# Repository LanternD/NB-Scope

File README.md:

# NB-Scope

Hardware and software design for NB-Scope.

NB-Scope is employed in our MobiCom 20 paper "Understanding Power Consumption of NB-IoT in the Wild: Tool and Large-scale Measuremen" [DOI](https://doi.org/10.1145/3372224.3419212).

Please check the README.md under the folders for more details.

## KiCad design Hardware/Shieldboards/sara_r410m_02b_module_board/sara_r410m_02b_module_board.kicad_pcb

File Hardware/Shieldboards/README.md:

# Important Note

- The majority of the modules here can be soldered by hand, except Quectel BG96 and uBlox SARA-R410M-02B.
  - If you solder the SARA-R410M-02B **by yourself** (customizing the stencil and applying the solder paste), instead of using the SMT service, you need to shrink the size of all the pads of the SARA-R410M-02B footprint! Otherwise they are likely to get short-circuited.
  - Before

  - After

- All the shieldboards have a RESET button for the module.
- There is a design compatibility issue in those modules with a "PWR_KEY" pin, including SARA-R410M-02B, BG96, BC26, and BC66. The pin requires an open collector transistor to enable, which I use different hardware designs to take care of it across different version of the board. Here is the summary:
  - Node mainboard v3.2 + BC26/BC66/SARA shieldboard: no modification needed.
  - Node mainboard v3.2 + SARA shieldboard: use GPIO_L4 as the `PWRKEY` control pin. The software code can handle this.
  - Node mainboard v3.1 + BC26/BC66/BG96 shieldboard: need to fixed by the `pwr_key_addon` in "Auxilliary Boards" folder (**Not recommended**).
  - Node mainboard v3.1 + SARA shieldboard: use GPIO_L4 as the `PWRKEY` control pin (**Not recommended**).

# Photos

Note: the pin headers in the photos face up, but in reality they should be soldered on the other side of the board, facing down, such that the shieldboard can be docked to the mainboard.

## Quectel BC26 (BC66) Shieldboard

Note: BC66 is almost identical to BC26 board, except for the swap between UART Tx and Rx pin.

## Quectel BC28 Shieldboard

## Quectel BC95/BC35 Shieldboard

## Gosuncn ME3616 Shieldboard

## Quectel BG96/BG36 Shieldboard

## uBlox SARA-R410M-02B Shieldboard

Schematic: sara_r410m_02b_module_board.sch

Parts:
C1, C2, C3, C4, C5, C6, C7, C8: 100nF; C_0603_1608Metric
D1: LED; LED_0805_2012Metric
J1: 1865; SMA_Antenna
J2: Left_Conn; PinHeader_1x22_P1.27mm_Vertical
J3: Right_Conn; PinHeader_1x22_P1.27mm_Vertical
J4: USB_DET_Conn; PinHeader_1x02_P1.27mm_Vertical
Q1, Q2: MMBT3904; SOT-23
R1: 0; R_0603_1608Metric
R2: 4.7k; R_0603_1608Metric
R3: 47k; R_0603_1608Metric
R5, R22: 2.2k; R_0603_1608Metric
SW1: SW_Push; SMD_Switch
T1: M_PWR_KEY; test_pad
U1: uBlox_SARA-R410M-02B; Ublox_SARA-R410M-02B
U2, U3: TXB0304RUT; Texas_R_PUQFN-N12

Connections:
/B_SPI_CLK-I2S_CLK: J2.7
/B_SPI_CS-I2S_CS: J2.8
/B_SPI_MISO-I2S_RXD: J2.5
/B_SPI_MOSI-I2S_WA: J2.6
/GPIO_L1: J2.3, U2.7
/GPIO_L2: J2.9, U2.8
/GPIO_L3: J2.21, U2.9
/GPIO_L4: J2.22, R2.2
/GPIO_R1: J3.8, U3.10
/GPIO_R2: J3.17
/GPIO_R3: J3.18
/M_ADC: J2.13
/M_AP_READY: J2.20
/M_AUX_UART_Rx: J3.14
/M_AUX_UART_Tx: J3.13
/M_DBG_UART_Rx: J3.12
/M_DBG_UART_TX: J3.11
/M_MAIN_UART_Rx: J2.15, U1.12 (TXD)
/M_MAIN_UART_Tx: J2.14, U1.13 (RXD)
/M_NET_LED: J3.15, U1.16 (GPIO1)
/M_PWRKEY: J2.16
/M_PWR_KEY_NEW: Q2.3, T1.1, U1.15 (PWR_ON)
/M_RESET: J2.17, U2.10
/M_RI: J3.16, U1.7 (RI)
/M_SCL: J3.10, U3.8
/M_SDA: J3.9, U3.9
/M_USB_DM: J2.12, U1.28 (USB_D-)
/M_USB_DP: J2.11, U1.29 (USB_D+)
/M_USB_VBUS: J2.10, J4.1
/M_VDD_OUT: C4.2, C7.2, J2.19, U1.4 (V_INT), U2.1, U2.12, U3.1, U3.12
/PSM_EINT: J2.18
/PSM_IND: J2.4
/SARA_GPIO2: U1.23 (GPIO2), U2.4
/SARA_GPIO3: U1.24 (GPIO3), U2.3
/SARA_GPIO5: U1.42 (GPIO5), U3.2
/SARA_GPIO6: U1.19 (GPIO6), U2.5
/SARA_RESET: C1.1, SW1.2, U1.18 (RESET_N), U2.2
/SARA_SCL: U1.27 (SCL), U3.4
/SARA_SDA: U1.26 (SDA), U3.3
/SARA_STATUS_LED: R22.2, U1.25 (GPIO4)
/SIM_CLK: J3.6, U1.38 (SIM_CLK)
/SIM_IO: J3.5, U1.39 (SIM_IO)
/SIM_RST: J3.4, U1.40 (SIM_RST)
/V_SIM: J3.3, U1.41 (VSIM)
GND: C1.2, C2.2, C3.2, C4.1, C5.1, C6.2, C7.1, C8.1, J1.GND1, J1.GND2, J1.GND3, J1.GND4, J3.7, J3.19, J3.20, J3.21, J3.22, Q1.2, Q2.2, R3.1, SW1.1, U1.1 (GND), U1.3 (GND), U1.5 (GND), U1.14 (GND), U1.20 (GND), U1.21 (GND), U1.22 (GND), U1.30 (GND), U1.32 (GND), U1.43 (GND), U1.50 (GND), U1.54 (GND), U1.55 (GND), U1.57 (GND), U1.58 (GND), U1.59 (GND), U1.60 (GND), U1.61 (GND), U1.63 (GND), U1.64 (GND), U1.65 (GND), U1.66 (GND), U1.67 (GND), U1.68 (GND), U1.69 (GND), U1.70 (GND), U1.71 (GND), U1.72 (GND), U1.73 (GND), U1.74 (GND), U1.75 (GND), U1.76 (GND), U1.77 (GND), U1.78 (GND), U1.79 (GND), U1.80 (GND), U1.81 (GND), U1.82 (GND), U1.83 (GND), U1.84 (GND), U1.85 (GND), U1.86 (GND), U1.87 (GND), U1.88 (GND), U1.89 (GND), U1.90 (GND), U1.91 (GND), U1.92 (GND), U1.93 (GND), U1.94 (GND), U1.95 (GND), U1.96 (GND), U2.6, U3.6
unnamed: C2.1, R1.2, U1.56 (ANT)
unnamed: C3.1, J1.P, R1.1
unnamed: D1.1 (K), Q1.3
unnamed: D1.2 (A), R5.2
unnamed: J4.2, U1.17 (VUSB_DET)
unnamed: Q1.1, R22.1
unnamed: Q2.1, R2.1, R3.2

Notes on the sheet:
Connectors to the module board
From Node Base
Reset Buttom Circuit
For right hand part
For left hand part
Note: no pull-up resistor needed (has internal one)
Note: The SARA uses the STUPID ITU-T V.24 recommendation. So the "RXD" on the module means the RXD of the MCU. It actually outputs data.

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
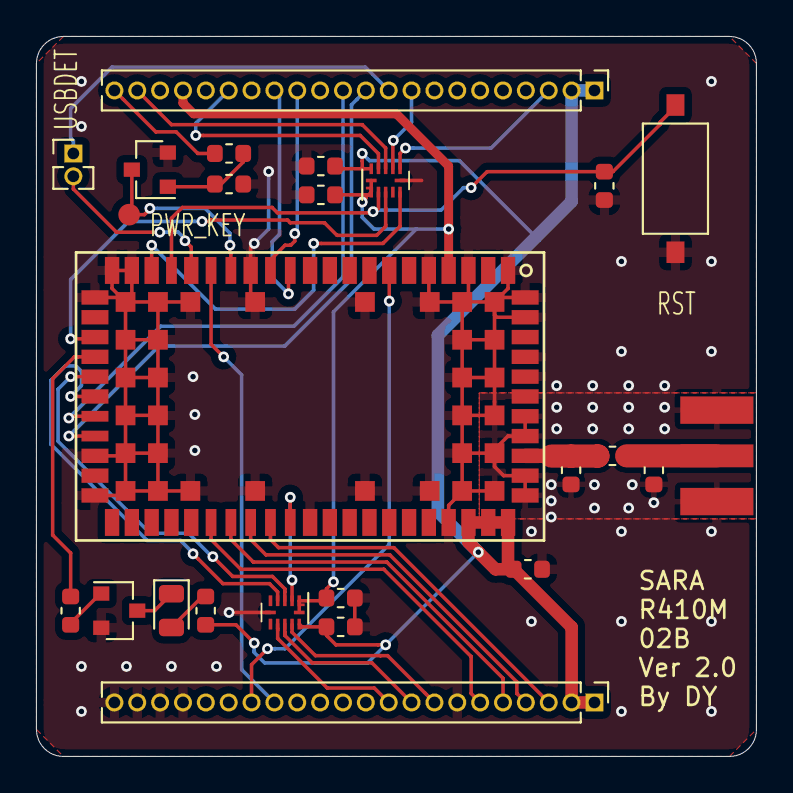
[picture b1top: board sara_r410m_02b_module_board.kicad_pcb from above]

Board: 2 copper layers, 40.0 x 40.0 mm, 25 parts (0 on the bottom side), 38 nets.

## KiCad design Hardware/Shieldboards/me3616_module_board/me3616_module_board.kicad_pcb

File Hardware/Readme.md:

# Hardware Guideline

## Overview

This folder contains the NB-Scope nodes hardware designs. Specifically, we have a folder for the mainboard, a folder for all the shieldboard for NB-Scope, and a folder for the auxilliary boards.

### Mainboard

The mainboard has 3 versions. **Please use ver 3.2**. The outdated versions are for reference only. They may work but not very stable. Ver 1.0 and 2.0 are not for NB-Scope projects, thus are omitted.

### Shieldboards

We have 7 types of shieldboard designs, supporting up to 9 types of different NB-IoT modules, including:

- Quectel BC28
- Quectel BC35
- Quectel BC26
- Quectel BC66
- Quectel BC95 (Not tested)
- Quectel BG36 (Not tested)
- Quectel BG96
- Gosuncn ME3616
- uBlox SARA-R410M-02B

(Quectel BG36/BG96 and Quectel BC35/BC95, have the same pin assignment, respectively.)

The module PCB project names should be straight-forward in the "Shieldboards" folder.

### Auxilliary boards

- Current sensing calibration board
- Firmware upgrade extension board
- Moulde benchmark extension board
- PWR_KEY addon

### Libraries

If you encounter missing symbol/footprint problem when opening the schematic or PCB files, please import them in the `Libraries` folder. The missing libraries should be a subset of the available footprints.

### Materials

I put the related documents related to hardware design here, including NB-IoT module summary and various datasheets.

## EDA environment

The software to open the projects is [KiCad](https://kicad-pcb.org/) (Pronounced as "key-cad").

PLEASE use the **Nightly-build** version of KiCad because the projects are created by that. The projects are not backward compatible.

To open the 3D viewer, click "View->3D Viewer" (<kbd>⌥+3</kbd> on Mac or <kbd>Alt+3</kbd> on other operating systems) in the `Pcbnew` software menu.

If you use the latest version of KiCad to open `.sch` files, `Eeschema`, the software component to edit schematic, will ask you to convert the `.sch` into `.kicad_sch`. Just go ahead and follow the instruction in KiCad.

You can generate all the files for fabrication in `Pcbnew` software module in KiCad.

## Project structure

- `<project_name>.pro`: project main file.
- `<project_name>.sch` or `<project_name>.kicad_sch`: project schematic design. If `.sch` and `.kicad_sch` co-exist, use the `.kicad_sch` one.
- `<project_name>.kicad_pcb`: project PCB design.
- `Exported Files` folder: exported/generated files from the projects, including Gerber files, bill of materials (BOM), positioning files (for SMT process), and other board 3D views or documents. I suggest you double check the project schematic and pcb designs, then generate these fabrication files again by yourself, instead of sending the Gerber files to manufacturers directly.

There are some KiCad generated backup or middle files. I forget to remove them before committing. You may ignore or edit them. They have the following patterns:

- `fp-info-cache`
- `<project name>-cache.lib`
- `<project name>-rescue.dcm`
- `<project name>-rescue.lib`
- `<project name>.kicad_pcb-bak`
- `<project name>.sch-bak`
- `sys-lib-table`

## Click into their corresponding folders for more details

If you have any questions, please send me an email to "yangdeli at msu.edu".

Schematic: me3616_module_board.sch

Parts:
C1, C2, C3, C7: 100nF; C_0603_1608Metric
J1: 1865; SMA_Antenna
J2: USB_V_BUS_EN; PinHeader_1x02_P1.27mm_Vertical
J12: Left_Conn; PinHeader_1x22_P1.27mm_Vertical
J13: Right_Conn; PinHeader_1x22_P1.27mm_Vertical
Q1, Q2: MMBT3904; SOT-23
R1: 0; R_0603_1608Metric
R2, R4: 4.7k; R_0603_1608Metric
R3, R5: 47k; R_0603_1608Metric
SW2: SW_Push; SMD_Switch
T2: ME3616_MAIN_RXD; test_pad
T3: ME3616_DBG_RXD; test_pad
T4: ME3616_MAIN_TXD; test_pad
T5: ME3616_DBG_TXD; test_pad
U1: ME3616; ZTE_ME3616

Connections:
+3V3: C1.1, J2.2, J12.1, J12.2, J13.1, J13.2, U1.31 (VCC_BB), U1.32 (VCC_RF)
/B_SPI_CLK-I2S_CLK: J12.7
/B_SPI_CS-I2S_CS: J12.8
/B_SPI_MISO-I2S_RXD: J12.5
/B_SPI_MOSI-I2S_WA: J12.6
/GPIO_L1: J12.3, U1.34 (GPIO1)
/GPIO_L2: J12.9, U1.35 (GPIO2)
/GPIO_L3: J12.21
/GPIO_L4: J12.22, R2.2
/GPIO_R1: J13.8
/GPIO_R2: J13.17
/GPIO_R3: J13.18
/ME3616_POWER_ON: Q2.3, U1.19 (POWER_ON)
/ME3616_RESET: Q1.3, U1.17 (RESET)
/M_ADC: J12.13
/M_AP_READY: J12.20
/M_AUX_UART_RX: J13.14
/M_AUX_UART_TX: J13.13
/M_DBG_UART_RX: J13.12, T3.1, U1.2 (UART_DEBUG_RXD)
/M_DBG_UART_TX: J13.11, T5.1, U1.1 (UART_BEBUG_TXD)
/M_MAIN_UART_RX: J12.15, T2.1, U1.10 (UART1_RXD)
/M_MAIN_UART_TX: J12.14, T4.1, U1.9 (UART1_TXD)
/M_NET_LED: J13.15, U1.21 (SYS_STATE)
/M_PWRKEY: J12.16
/M_RESET: C7.1, J12.17, R4.2, SW2.2
/M_RI: J13.16
/M_SCL: J13.10
/M_SDA: J13.9
/M_USB_DM: J12.12, U1.39 (USB_DM)
/M_USB_DP: J12.11, U1.40 (USB_DP)
/M_USB_VBUS: J12.10
/M_VDD_OUT: J12.19, U1.20 (VCC1V8_OUT)
/PSM_EINT: J12.18, U1.18 (WAKEUP_IN)
/PSM_IND: J12.4
/SIM_CLK: J13.6, U1.13 (USIM_CLK)
/SIM_IO: J13.5, U1.14 (USIM_DATA)
/SIM_RST: J13.4, U1.12 (USIM_RESET)
/V_SIM: J13.3, U1.15 (USIM_VCC)
GND: C1.2, C2.2, C3.2, C7.2, J1.GND1, J1.GND2, J1.GND3, J1.GND4, J13.7, J13.19, J13.20, J13.21, J13.22, Q1.2, Q2.2, R3.1, R5.1, SW2.1, U1.22 (GND), U1.23 (GND), U1.25 (GND), U1.26 (GND), U1.28 (GND), U1.29 (GND), U1.30 (GND)
unnamed: C2.1, R1.2, U1.27 (MAIN_ANT)
unnamed: C3.1, J1.P, R1.1
unnamed: J2.1, U1.33 (VBUS_3V3)
unnamed: Q1.1, R4.1, R5.2
unnamed: Q2.1, R2.1, R3.2

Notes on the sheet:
Note: The ME3616 uses the LED on the base board.
Connectors to the module board
From Node Base
ME3616 Onboard Reset Circuit (No pull-up needed, but add one if this circuit doesn't work)

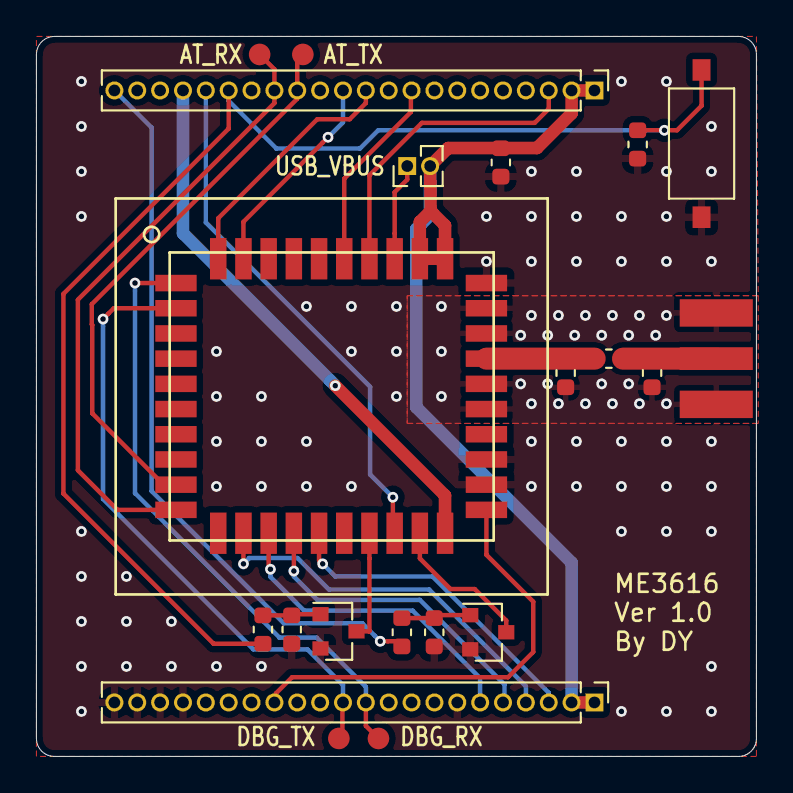
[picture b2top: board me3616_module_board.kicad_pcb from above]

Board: 2 copper layers, 40.0 x 40.0 mm, 21 parts (0 on the bottom side), 26 nets.

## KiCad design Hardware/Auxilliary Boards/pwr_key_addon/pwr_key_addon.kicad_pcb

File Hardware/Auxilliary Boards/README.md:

# Introduction

Auxilliary boards are used to extend the capability of the mainboard and shieldboard, as well as to calibrate the current sensors.

# Current Calibration Board

Since the 0.1 Ohm current sensing resistors are different, the current sensing should be calibrated as per mainboard. 

You need a series of resistors for this board. The actual resistance does not matter. We just compare the sensor reading with the digital multimeter or power monitor reading.

## How to calibrate

Solder the 1.27 mm pitch headers according to the image above. Then follow the instruction to test the output.

Before calibration, make sure the embedded code runs the "current sensing demo" (`void run_demo8_i_bus_sensing()` in `Software/field-test-control/Src/fm_demo.c`). Check the `main.c` as well. 

The mainboard should be connected to the PC via USB, then the PC should open a serial console to read the data from the board.

Steps:

1. See the figure above.
2. See the figure above.
3. Read and record the external current measurement device output (mA).
4. Read and record the INA226 output via the USB UART. The board will output the current register reading once per second.
5. Repeat the above steps for resistors from 13.3 Ohm to 165 Ohm. The 11 Ohm is not recommended. Do not try the 5.6 Ohm.
6. Calculation as follows:
  
  1. Multiply the register value by 0.018311 to get the current reading of INA226. (Note: if the output is already the current value, you don't need to do this conversion, depending on the output of the embedded program.)
  2. Divide the INA226 current by the meter reading current to get a ratio.
  3. Multiply the ratio with 2778 (the preset INA226 calibration register value) to get the new calibration register value. 
  4. Average all the calibration values to get the final calibration value.
  
Here is a table showing the measurement and calculation example for one of our board.

| Expected current (mA) | Meter reading (mA) | INA226 register reading | Calculated INA226 current (mA) | New calibration value |
|-----------------------|--------------------|-------------------------|--------------------------------|-----------------------|
|                    20 |               20.0 |                    1089 |                      19.940679 |              2786.264 |
|                  48.5 |               49.0 |                    2659 |                      48.688949 |              2795.747 |
|                   100 |               99.5 |                    5484 |                     100.417524 |              2752.517 |
|                   150 |              149.0 |                    8235 |                     150.791085 |              2745.003 |
|                   200 |              198.0 |                   10974 |                     200.944914 |              2737.287 |
|                   248 |                244 |                   13487 |                     246.960457 |              2744.699 |

The final calibration value is the average of the last column, resulting in 2760.

The value you get should not be too far from these value above. The final calibration value is around 2700 - 2900. For the same batch of boards, the standard deviation is less than 50. If you use a different batch of current sensing resistor, the value can deviate up to 150. 

**The new current calibration value should be written into the onboard EEPROM before node deployment.**

Note: you need to calibrate EVERY mainboard.

# Module Benchmark Extension Board

An upgraded version of "Firmware Upgrade Extension Board". It docks the shieldboard for the "real-time benchmark mode" of NB-Scope. It can be used to upgrade the NB-IoT module firmware as well. Basically it pinouts all the necessary connectivity of the UE module, such that we can connect them to other peripherals, such as power monitor and UART. 

The two pin headers are compatible with the mainboard.

The "EXT3V3" is used to connect to the power monitor. For example, the RED terminal of the monitor is connected to the EXT3V3, and the BLACK terminal is connected to the 3V3, repectively. "EXTGND" is likewise.

# Firmware Upgrade Extension Board

This is the predecessor of "Module Benchmark Extension Board". Generally you can ignore this one.

# PWRKEY Addon

A tiny board that simply has a BJT on it. It is used to fixed the PWRKEY pin on the UE modules before ver 3.2 mainboard. If you use the latest version of the mainboard, you can ignore this.

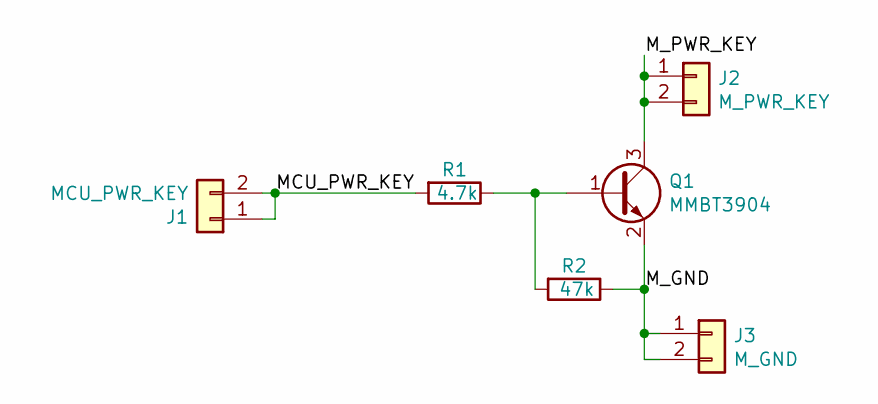
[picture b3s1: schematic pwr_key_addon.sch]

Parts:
J1: MCU_PWR_KEY; PinHeader_1x02_P1.27mm_Vertical
J2: M_PWR_KEY; PinHeader_1x02_P1.27mm_Vertical
J3: M_GND; PinHeader_1x02_P1.27mm_Vertical
Q1: MMBT3904; SOT-23
R1: 4.7k; R_0805_2012Metric
R2: 47k; R_0805_2012Metric

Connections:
/MCU_PWR_KEY: J1.1, J1.2, R1.2
/M_GND: J3.1, J3.2, Q1.2 (E), R2.1
/M_PWR_KEY: J2.1, J2.2, Q1.3 (C)
unnamed: Q1.1 (B), R1.1, R2.2

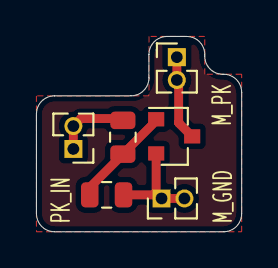
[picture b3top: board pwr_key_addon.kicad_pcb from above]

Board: 2 copper layers, 11.4 x 10.8 mm, 6 parts (0 on the bottom side), 4 nets.

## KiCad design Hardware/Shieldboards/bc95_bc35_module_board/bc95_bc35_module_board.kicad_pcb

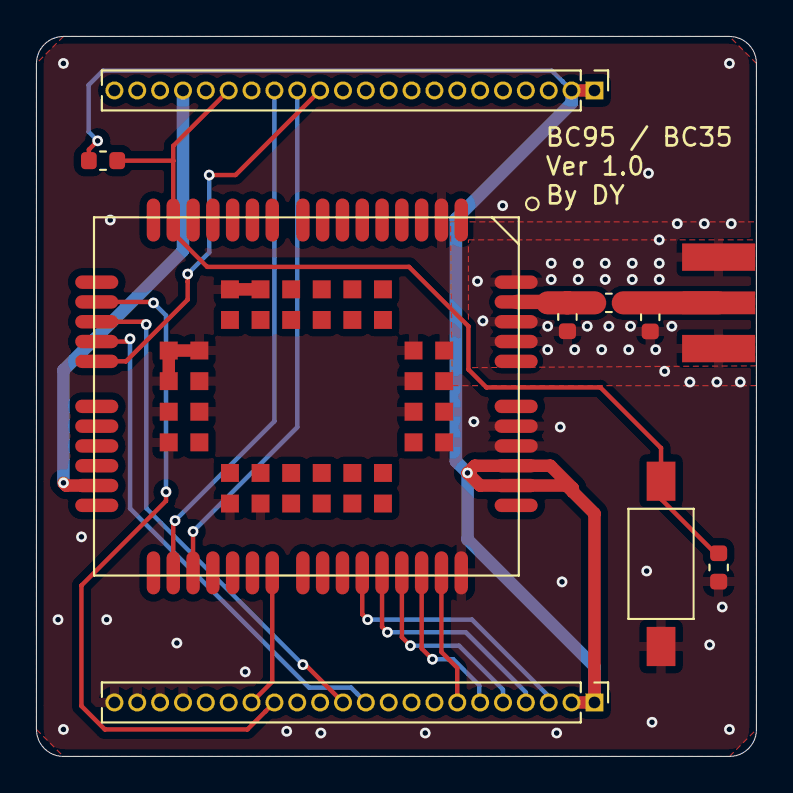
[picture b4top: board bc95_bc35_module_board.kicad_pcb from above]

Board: 2 copper layers, 40.0 x 40.0 mm, 10 parts (0 on the bottom side), 18 nets.

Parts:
C1, C2, C3: 100nF; C_0603_1608Metric
J1: 1865; SMA_Antenna
J2: Left_Conn; PinHeader_1x22_P1.27mm_Vertical
J3: Right_Conn; PinHeader_1x22_P1.27mm_Vertical
R1: 0; R_0603_1608Metric
R2: 10k; R_0603_1608Metric
SW1: SW_Push; SW_SPST_FSMSM
U1: BC95; Quectel_BC95_BC35

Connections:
+3V3: J2.1, J2.2, J3.1, J3.2, R2.2, U1.45, U1.46
/M_ADC: J2.13, U1.21
/M_DBG_UART_Rx: J3.12, U1.19
/M_DBG_UART_TX: J3.11, U1.20
/M_MAIN_UART_Rx: J2.15, U1.29
/M_MAIN_UART_Tx: J2.14, U1.30
/M_NET_LED: J3.15, U1.18
/M_RESET: C1.1, J2.17, R2.1, SW1.2, U1.15
/M_RI: J3.16, U1.34
/M_VDD_OUT: J2.19, U1.26
/SIM_CLK: J3.6, U1.41
/SIM_GND: J3.7, U1.42
/SIM_IO: J3.5, U1.40
/SIM_RST: J3.4, U1.39
/V_SIM: J3.3, U1.38
GND: C1.2, C2.2, C3.2, J1.GND1, J1.GND2, J1.GND3, J1.GND4, J3.19, J3.20, J3.21, J3.22, SW1.1, U1.2, U1.43, U1.47, U1.48, U1.51, U1.52, U1.54, U1.59, U1.60, U1.61, U1.62, U1.63, U1.64, U1.65, U1.66, U1.71, U1.72, U1.73, U1.74, U1.81, U1.82, U1.83, U1.92, U1.93, U1.94
unnamed: C2.1, R1.2, U1.53
unnamed: C3.1, J1.P, R1.1

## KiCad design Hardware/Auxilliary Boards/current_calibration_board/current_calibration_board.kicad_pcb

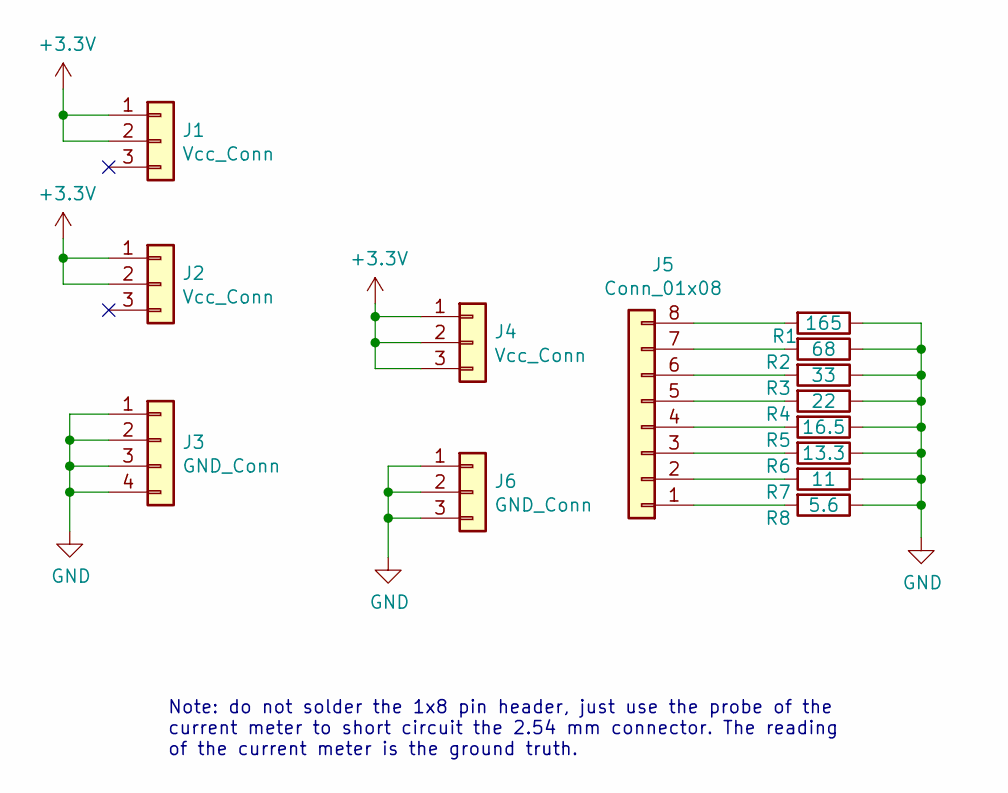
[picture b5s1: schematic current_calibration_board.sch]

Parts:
J1, J2: Vcc_Conn; PinHeader_1x03_P1.27mm_Vertical
J3: GND_Conn; PinHeader_1x04_P1.27mm_Vertical
J4: Vcc_Conn; PinHeader_1x03_P2.54mm_Vertical
J5: Conn_01x08; PinHeader_1x08_P2.54mm_Vertical
J6: GND_Conn; PinHeader_1x03_P2.54mm_Vertical
R1: 165; R_0805_2012Metric_Pad1.15x1.40mm_HandSolder
R2: 68; R_1206_3216Metric_Pad1.42x1.75mm_HandSolder
R3: 33; R_1210_3225Metric_Pad1.42x2.65mm_HandSolder
R4: 22; R_1210_3225Metric_Pad1.42x2.65mm_HandSolder
R5: 16.5; R_2512_6332Metric_Pad1.52x3.35mm_HandSolder
R6: 13.3; R_2512_6332Metric_Pad1.52x3.35mm_HandSolder
R7: 11; R_2512_6332Metric_Pad1.52x3.35mm_HandSolder
R8: 5.6; Resistor_SMD_1225_2W

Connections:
+3V3: J1.1, J1.2, J2.1, J2.2, J4.1, J4.2, J4.3
GND: J3.1, J3.2, J3.3, J3.4, J6.1, J6.2, J6.3, R1.1, R2.1, R3.1, R4.1, R5.1, R6.1, R7.1, R8.1
unnamed: J5.1, R8.2
unnamed: J5.2, R7.2
unnamed: J5.3, R6.2
unnamed: J5.4, R5.2
unnamed: J5.5, R4.2
unnamed: J5.6, R3.2
unnamed: J5.7, R2.2
unnamed: J5.8, R1.2

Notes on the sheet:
Note: do not solder the 1x8 pin header, just use the probe of the current meter to short circuit the 2.54 mm connector. The reading of the current meter is the ground truth.

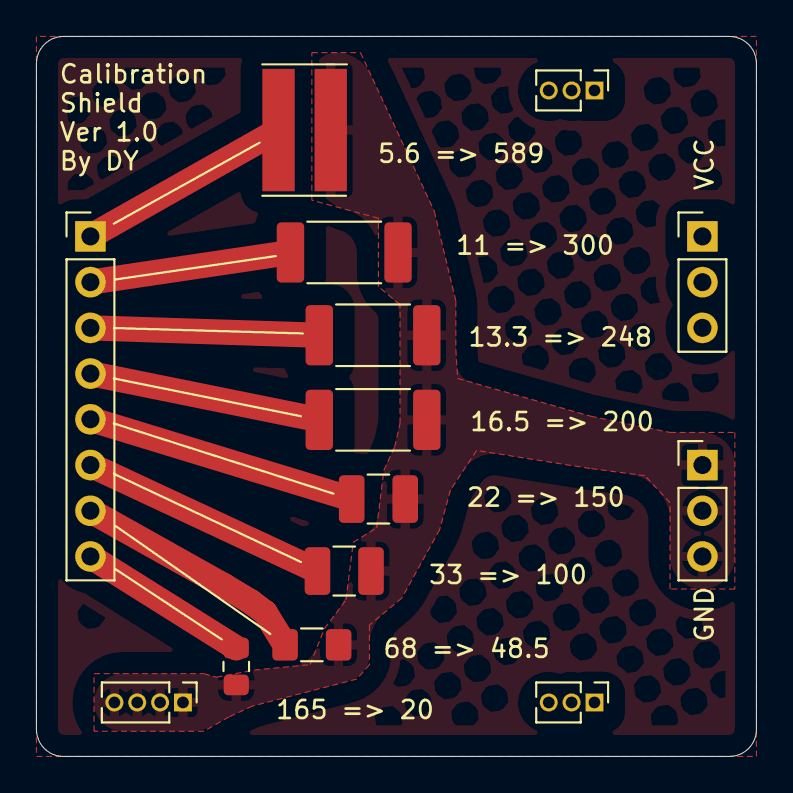
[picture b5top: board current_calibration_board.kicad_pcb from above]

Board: 2 copper layers, 40.0 x 40.0 mm, 14 parts (0 on the bottom side), 10 nets.

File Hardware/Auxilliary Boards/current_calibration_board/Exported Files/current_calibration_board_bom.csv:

"Id";"Designator";"Package";"Quantity";"Designation";"Supplier and ref";
1;"REF**";"KiCad-Logo2_5mm_SilkScreen";1;"KiCad-Logo2_5mm_SilkScreen";;;
2;"G***";"Cat-Logo";1;"LOGO";;;
3;"J6";"PinHeader_1x03_P2.54mm_Vertical";1;"GND_Conn";;;
4;"R8";"Resistor_SMD_1225_2W";1;"5.6";;;
5;"R7";"R_2512_6332Metric_Pad1.52x3.35mm_HandSolder";1;"11";;;
6;"R6";"R_2512_6332Metric_Pad1.52x3.35mm_HandSolder";1;"13.3";;;
7;"R5";"R_2512_6332Metric_Pad1.52x3.35mm_HandSolder";1;"16.5";;;
8;"R4";"R_1210_3225Metric_Pad1.42x2.65mm_HandSolder";1;"22";;;
9;"R3";"R_1210_3225Metric_Pad1.42x2.65mm_HandSolder";1;"33";;;
10;"R2";"R_1206_3216Metric_Pad1.42x1.75mm_HandSolder";1;"68";;;
11;"R1";"R_0805_2012Metric_Pad1.15x1.40mm_HandSolder";1;"165";;;
12;"J5";"PinHeader_1x08_P2.54mm_Vertical";1;"Conn_01x08";;;
13;"J4";"PinHeader_1x03_P2.54mm_Vertical";1;"Vcc_Conn";;;
14;"J3";"PinHeader_1x04_P1.27mm_Vertical";1;"GND_Conn";;;
15;"J2,J1";"PinHeader_1x03_P1.27mm_Vertical";2;"Vcc_Conn";;;

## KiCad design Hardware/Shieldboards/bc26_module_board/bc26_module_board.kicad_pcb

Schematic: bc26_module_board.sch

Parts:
C1, C2, C3, C4, C5, C7: 100nF; C_0603_1608Metric
J1: 1865; SMA_Antenna
J12: Left_Conn; PinHeader_1x22_P1.27mm_Vertical
J13: Right_Conn; PinHeader_1x22_P1.27mm_Vertical
R1: 0; R_0603_1608Metric
R11: 10k; R_0603_1608Metric
SW2: SW_Push; SW_SPST_FSMSM
U1: BC66; Quectel_BC66
U2: TXB0304RUT; Texas_R_PUQFN-N12

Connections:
/B_SPI_CLK-I2S_CLK: J12.7, U2.9
/B_SPI_CS-I2S_CS: J12.8, U2.10
/B_SPI_MISO-I2S_RXD: J12.5, U2.7
/B_SPI_MOSI-I2S_WA: J12.6, U2.8
/GPIO_L1: J12.3
/GPIO_L2: J12.9
/GPIO_L3: J12.21
/GPIO_L4: J12.22
/GPIO_R1: J13.8
/GPIO_R2: J13.17
/GPIO_R3: J13.18
/M_ADC: J12.13, U1.9 (ADC0)
/M_AP_READY: J12.20
/M_AUX_UART_Rx: J13.14, U1.28 (RXD_AUX)
/M_AUX_UART_Tx: J13.13, U1.29 (TXD_AUX)
/M_DBG_UART_Rx: J13.12, U1.38 (RXD_DBG)
/M_DBG_UART_TX: J13.11, U1.39 (TXD_DBG)
/M_MAIN_UART_Rx: J12.15, U1.17 (RXD)
/M_MAIN_UART_Tx: J12.14, U1.18 (TXD)
/M_NET_LED: J13.15, U1.16 (NETLIGHT)
/M_PWRKEY: J12.16, U1.7 (PWRKEY)
/M_RESET: C7.1, J12.17, R11.1, SW2.2, U1.15 (~RESET)
/M_RI: J13.16, U1.20 (RI)
/M_SCL: J13.10
/M_SDA: J13.9
/M_SPI_CLK-I2S_CLK: U1.5 (SPI_SCLK), U2.3
/M_SPI_CS-I2S_CS: U1.6 (SPI_CS), U2.2
/M_SPI_MISO-I2S_RXD: U1.3 (SPI_MISO), U2.5
/M_SPI_MOSI-I2S_WA: U1.4 (SPI_MOSI), U2.4
/M_USB_DM: J12.12
/M_USB_DP: J12.11
/M_USB_VBUS: J12.10
/M_VDD_OUT: C4.1, J12.19, U1.24 (VDD_EXT), U2.1, U2.12
/PSM_EINT: J12.18, U1.19 (PSM_EINT)
/PSM_IND: J12.4
/SIM_CLK: J13.6, U1.13 (SIM_CLK)
/SIM_GND: J13.7, U1.10 (SIM_GND)
/SIM_IO: J13.5, U1.11 (SIM_DATA)
/SIM_RST: J13.4, U1.12 (SIM_RST)
/V_SIM: J13.3, U1.14 (SIM_VDD)
GND: C1.2, C2.2, C3.2, C4.2, C5.2, C7.2, J1.GND1, J1.GND2, J1.GND3, J1.GND4, J13.19, J13.20, J13.21, J13.22, SW2.1, U1.1 (GND), U1.27 (GND), U1.34 (GND), U1.36 (GND), U1.37 (GND), U1.40 (GND), U1.41 (GND), U2.6
unnamed: C2.1, R1.2, U1.35 (RF_ANT)
unnamed: C3.1, J1.P, R1.1

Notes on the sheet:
BC28 Reset Circuit
From Node Base
Connectors to the module board
Note: VCCA is the low voltage side (from module) VCCB is the high voltage side (from base)

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
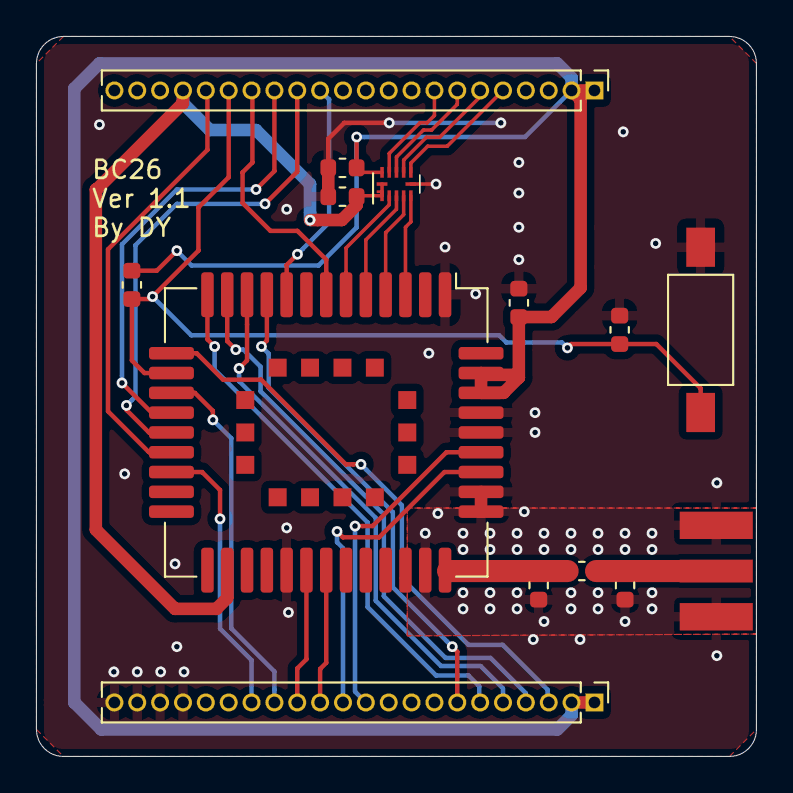
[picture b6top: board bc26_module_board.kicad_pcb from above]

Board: 2 copper layers, 40.0 x 40.0 mm, 14 parts (0 on the bottom side), 30 nets.

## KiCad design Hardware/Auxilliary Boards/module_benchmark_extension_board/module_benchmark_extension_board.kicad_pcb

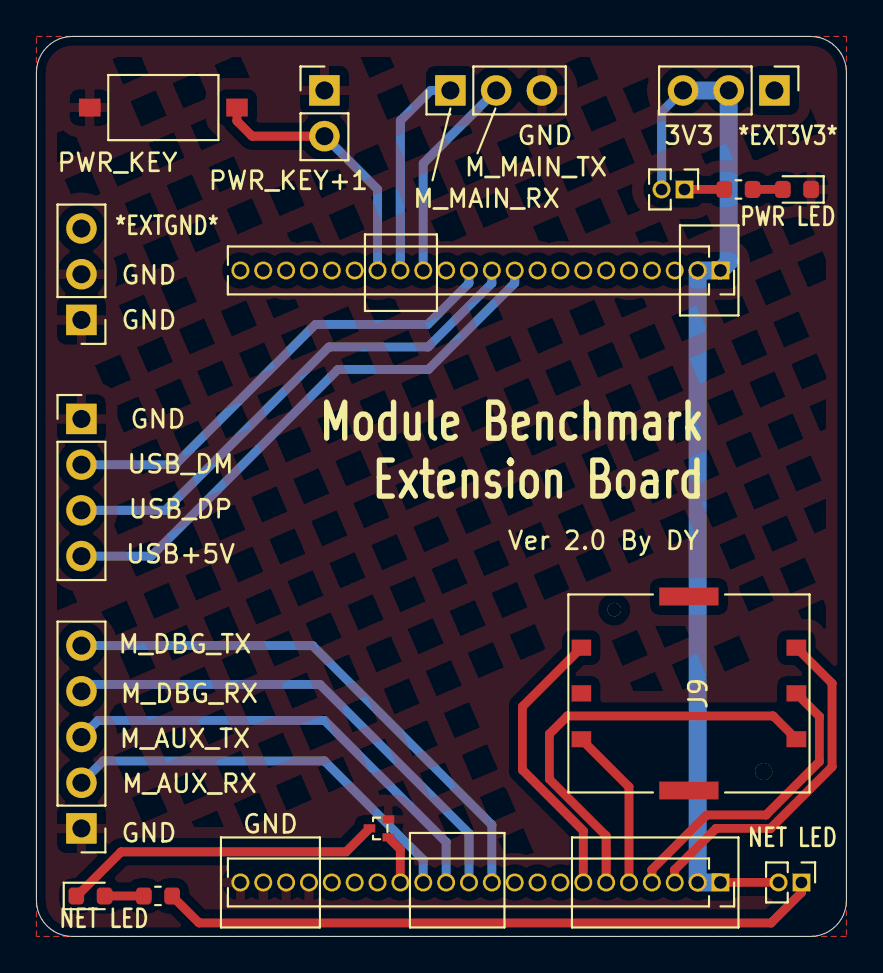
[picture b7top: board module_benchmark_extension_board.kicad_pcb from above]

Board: 2 copper layers, 45.0 x 50.0 mm, 17 parts (0 on the bottom side), 23 nets.

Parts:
D1, D2: LED; LED_0603_1608Metric
J1: MAIN_UART_CONN; PinHeader_1x03_P2.54mm_Vertical
J2: Left_Conn; PinSocket_1x22_P1.27mm_Vertical
J3: Right_Conn; PinSocket_1x22_P1.27mm_Vertical
J4: PWR_KEY_TO_GND_CONN; PinHeader_1x02_P2.54mm_Vertical
J5: VCC_CONN; PinHeader_1x03_P2.54mm_Vertical
J6: GND_CONN; PinHeader_1x03_P2.54mm_Vertical
J7: DBG_UART_CONN; PinHeader_1x05_P2.54mm_Vertical
J8: USB_CONN; PinHeader_1x04_P2.54mm_Vertical
J9: SIM_Card; XUNPU_SMN-304
J10: PWR_LED_SW; PinHeader_1x02_P1.27mm_Vertical
J11: NET_LED_SW; PinHeader_1x02_P1.27mm_Vertical
Q1: DTC143Z; SOT-723
R1, R2: 2.2k; R_0603_1608Metric
SW1: PWR_KEY_TO_GND_BTN; SMD_Switch

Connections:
+3V3: J2.1, J2.2, J3.1, J3.2, J5.2, J5.3, J10.2, J11.2
/M_AUX_UART_Rx: J3.14, J7.2
/M_AUX_UART_Tx: J3.13, J7.3
/M_DBG_UART_Rx: J3.12, J7.4
/M_DBG_UART_TX: J3.11, J7.5
/M_MAIN_UART_Rx: J1.1, J2.15
/M_MAIN_UART_Tx: J1.2, J2.14
/M_NET_LED: J3.15, Q1.1
/M_PWRKEY: J2.16, J4.2, SW1.2
/M_USB_DM: J2.12, J8.2
/M_USB_DP: J2.11, J8.3
/M_USB_VBUS: J2.10, J8.4
/SIM_CLK: J3.6, J9.3
/SIM_GND: J3.7, J9.5
/SIM_IO: J3.5, J9.7
/SIM_RST: J3.4, J9.2
/V_SIM: J3.3, J9.1
GND: D1.1, J1.3, J3.19, J3.20, J3.21, J3.22, J4.1, J6.1, J6.2, J7.1, J8.1, Q1.2, SW1.1
unnamed: D1.2, R1.1
unnamed: D2.1, Q1.3
unnamed: D2.2, R2.1
unnamed: J10.1, R1.2
unnamed: J11.1, R2.2
